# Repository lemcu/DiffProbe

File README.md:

DiffProbe
=========

Easy to construct differential probe for oscilloscope. Supports selectable 1x, 100x and 1000x gain. 

(c) 2013-2014 http://lemcu.org

<br />This work is licensed under a <a rel="license" href="http://creativecommons.org/licenses/by-sa/3.0/deed.en_US">Creative Commons Attribution-ShareAlike 3.0 Unported License</a>.

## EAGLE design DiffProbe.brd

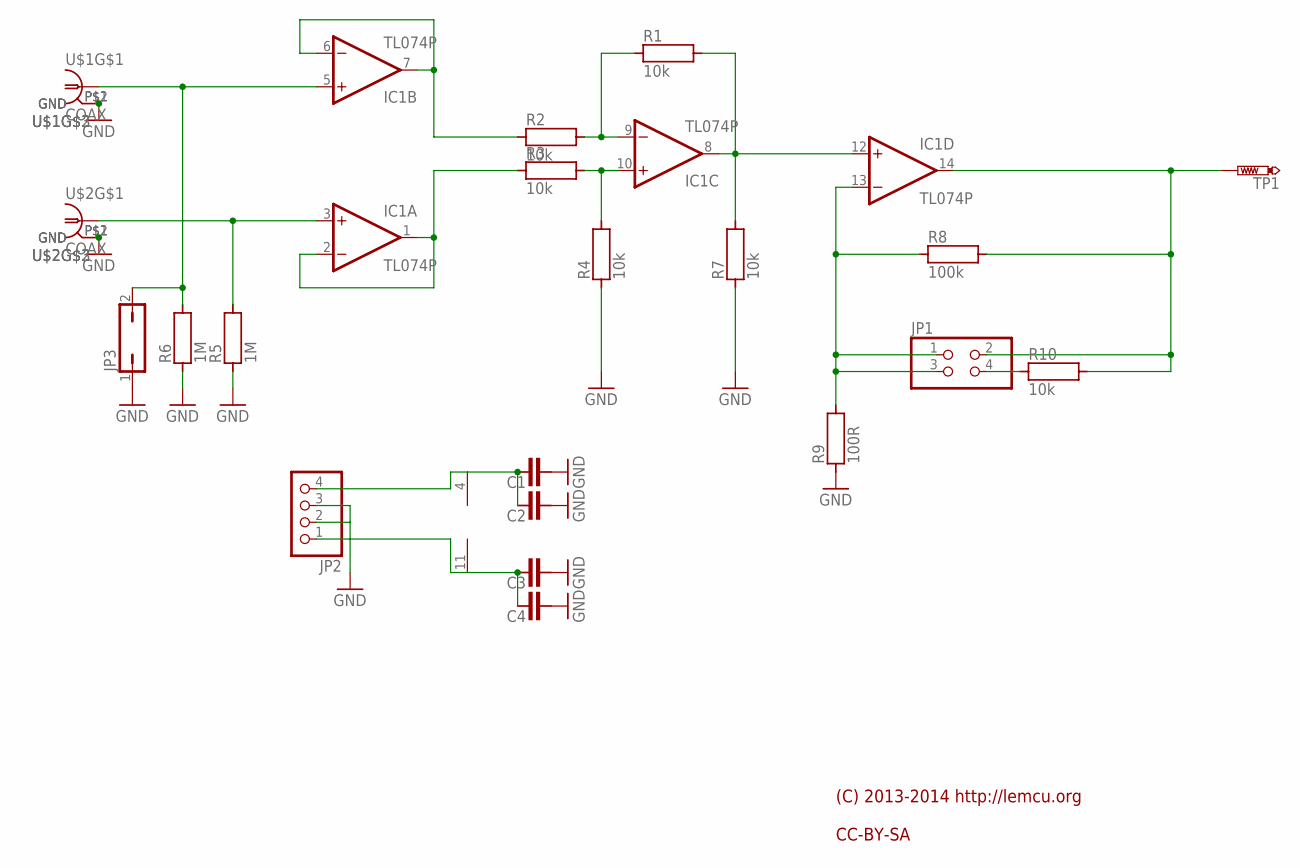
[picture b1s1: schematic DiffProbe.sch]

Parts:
C1, C3: C0603
C2, C4: C1206
IC1: TL074P; DIL14
JP1: PINHD-2X2; 2X02
JP2: PINHD-1X4; 1X04
JP3: JP1Q; JP1
R1, R2, R3, R4, R7, R10: 10k; R0603
R5, R6: 1M; R0603
R8: 100k; R0603
R9: 100R; R0603
TP1: PTR1B1,27; B1,27
U$1, U$2: COAX; COAX_GND

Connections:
GND: C1.1, C2.1, C3.1, C4.1, JP2.2, JP2.3, JP3.1, R4.1, R5.1, R6.1, R7.1, R9.1, U$1.4 (GND), U$1.P$1 (GND), U$1.P$2 (GND), U$2.4 (GND), U$2.P$1 (GND), U$2.P$2 (GND)
unnamed: IC1.10 (+IN), R3.2, R4.2
unnamed: IC1.9 (-IN), R1.1, R2.2
unnamed: JP1.4, R10.1
unnamed: IC1.8 (OUT), IC1.12 (+IN), R1.2, R7.2
unnamed: IC1.6 (-IN), IC1.7 (OUT), R2.1
unnamed: IC1.1 (OUT), IC1.2 (-IN), R3.1
unnamed: IC1.3 (+IN), R5.2, U$2.3 (1)
unnamed: IC1.5 (+IN), JP3.2, R6.2, U$1.3 (1)
unnamed: C3.2, C4.2, IC1.11 (V-), JP2.1
unnamed: C1.2, C2.2, IC1.4 (V+), JP2.4
unnamed: IC1.14 (OUT), JP1.2, R8.2, R10.2, TP1.TP
unnamed: IC1.13 (-IN), JP1.1, JP1.3, R8.1, R9.2

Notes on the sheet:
(C) 2013-2014 http://lemcu.org CC-BY-SA

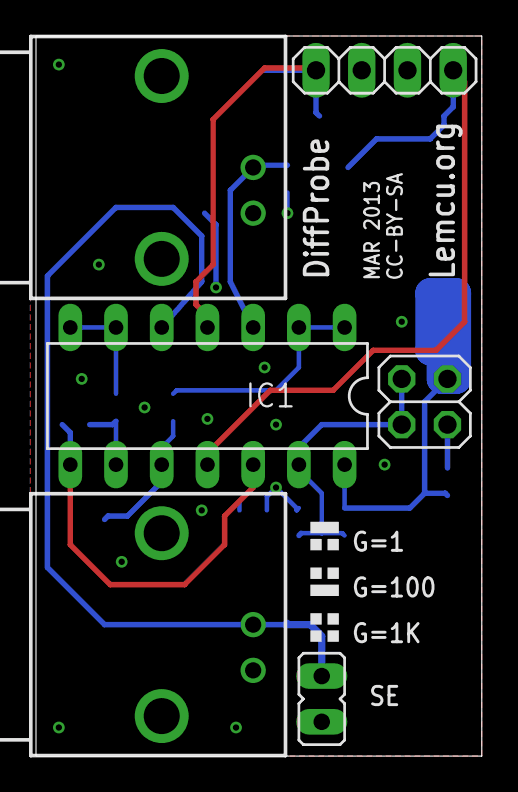
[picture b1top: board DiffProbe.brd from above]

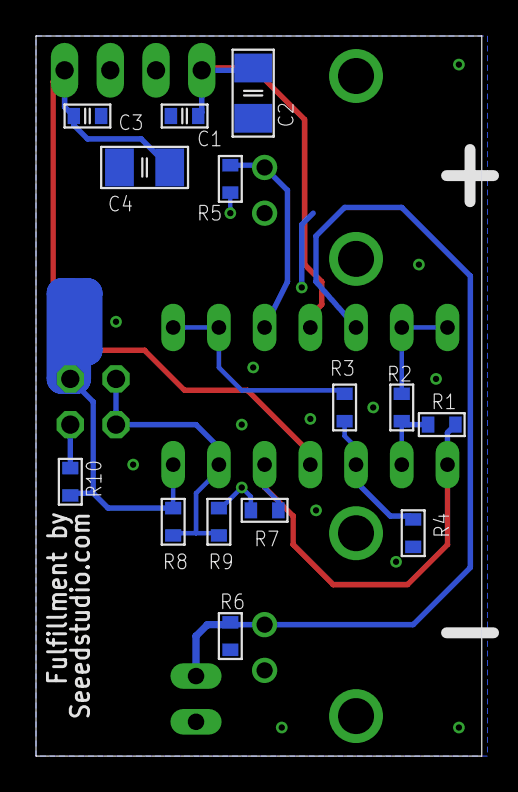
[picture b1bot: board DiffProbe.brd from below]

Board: 2 copper layers, 24.8 x 40.0 mm, 21 parts (15 on the bottom side), 13 nets.

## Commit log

2014-04-24 Schematic and Board - First Release
